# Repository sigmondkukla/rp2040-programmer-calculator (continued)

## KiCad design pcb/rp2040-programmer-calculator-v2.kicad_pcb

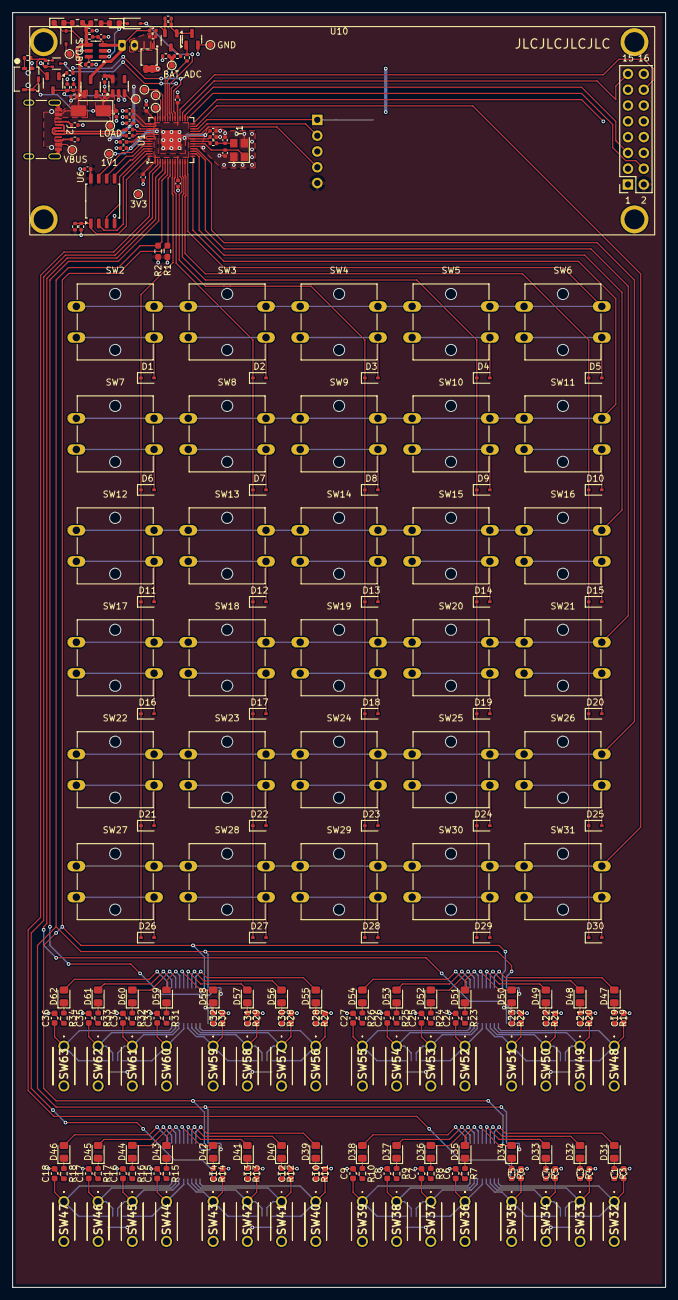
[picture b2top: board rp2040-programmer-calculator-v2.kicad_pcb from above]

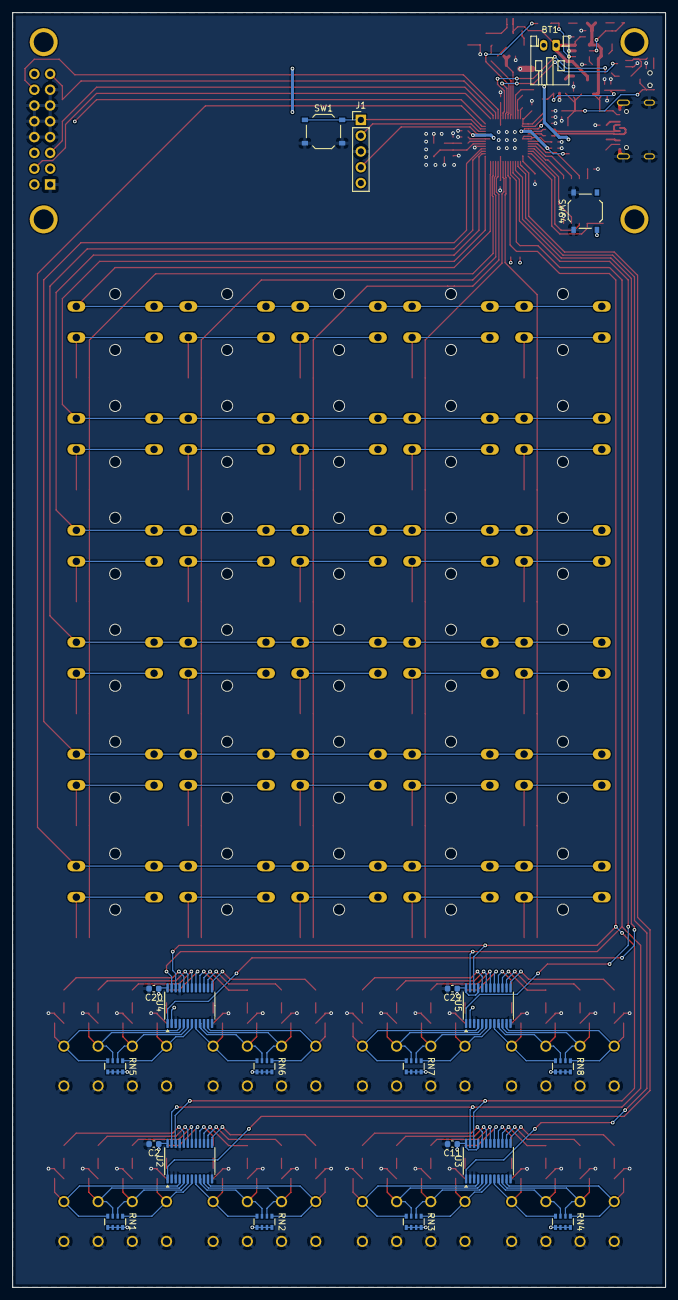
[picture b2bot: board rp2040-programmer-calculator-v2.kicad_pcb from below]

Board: 2 copper layers, 105.0 x 205.0 mm, 283 parts (20 on the bottom side), 196 nets.

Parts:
BT1: 3.7V; JST_PH_S2B-PH-K_1x02_P2.00mm_Horizontal_Reverse_Polarity
C1, C2, C3, C4, C5, C6, C7, C8, C9, C10, C11, C12, C13, C14, C15, C16, C17, C18, C19, C20, C21, C22, C23, C24, C25, C26, C27, C28, C29, C30, C31, C32, C33, C34, C35, C36: 100n; C_0603_1608Metric
C37, C47, C48, C49, C50, C51, C52, C56, C57, C58: 100n; C_0402_1005Metric
C38, C39: 15p; C_0402_1005Metric
C40, C43: 10u; C_0402_1005Metric
C41, C42, C44, C54, C55: 1u; C_0402_1005Metric
C45: 100p; C_0402_1005Metric
C46: 0.1u; C_0402_1005Metric
C53: 470n; C_0402_1005Metric
D1, D2, D3, D4, D5, D6, D7, D8, D9, D10, D11, D12, D13, D14, D15, D16, D17, D18, D19, D20, D21, D22, D23, D24, D25, D26, D27, D28, D29, D30, D66: 1N4148WS; D_SOD-323
D31, D32, D33, D34, D35, D36, D37, D38, D39, D40, D41, D42, D43, D44, D45, D46, D47, D48, D49, D50, D51, D52, D53, D54, D55, D56, D57, D58, D59, D60, D61, D62: IN-S85AT5B; LED_0805_2012Metric_Pad1.15x1.40mm_HandSolder
D63: SS14; D_SMA
D64, D65: KT-0603R; LED_0603_1608Metric
D67: DNP; D_SOD-323
D68: BAT54C; SOT-23-3
J1: Pin Header 1x05 P2.54mm; PinHeader_1x05_P2.54mm_Vertical
J2: USB4105-GF-A; USB_C_Receptacle_GCT_USB4105-xx-A_16P_TopMnt_Horizontal
Q1: AO3401A; SOT-23-3
Q2: BSS84; SOT-23-3
Q3: MMBT3904; SOT-23
Q4: DMG1012T; SOT-523
R1, R2: 4.7k; R_0603_1608Metric_Pad0.98x0.95mm_HandSolder
R3, R4, R5, R6, R7, R8, R9, R10, R11, R12, R13, R14, R15, R16, R17, R18, R19, R20, R21, R22, R23, R24, R25, R26, R27, R28, R29, R30, R31, R32, R33, R34: 270; R_0603_1608Metric
R35, R47, R50, R51: 10k; R_0402_1005Metric
R36, R41, R48, R52, R54: 1k; R_0402_1005Metric
R37, R38: 5.1k; R_0402_1005Metric
R39, R40: 27; R_0402_1005Metric
R42, R43, R53, R55: 100k; R_0402_1005Metric
R44: 2k; R_0402_1005Metric
R45, R46: 2k; R_0603_1608Metric
R49: 330k; R_0402_1005Metric
RN1, RN2, RN3, RN4, RN5, RN6, RN7, RN8: DNP; R_Array_Convex_4x0603
SW1, SW64: PTS526SM20SMTR21 LFS; SW_Push_1P1T_XKB_TS-1187A
SW2, SW3, SW4, SW5, SW6, SW7, SW8, SW9, SW10, SW11, SW12, SW13, SW14, SW15, SW16, SW17, SW18, SW19, SW20, SW21, SW22, SW23, SW24, SW25, SW26, SW27, SW28, SW29, SW30, SW31: B3F; SW_SPST_Omron_B3F-40xx
SW32, SW33, SW34, SW35, SW36, SW37, SW38, SW39, SW40, SW41, SW42, SW43, SW44, SW45, SW46, SW47, SW48, SW49, SW50, SW51, SW52, SW53, SW54, SW55, SW56, SW57, SW58, SW59, SW60, SW61, SW62, SW63: PTS636SL50 LFS; PTS636SL50LFS
SW65: R-667799; R-667799_MIT
TP1: TEST_GPIO27_ADC1; TestPoint_Pad_D1.0mm
TP2: TEST_GPIO28_ADC2; TestPoint_Pad_D1.0mm
TP3: TEST_GPIO29_ADC3; TestPoint_Pad_D1.0mm
TP4: TEST_3V3; TestPoint_Pad_D1.0mm
TP5: TEST_1V1; TestPoint_Pad_D1.0mm
TP6: TEST_VBUS; TestPoint_Pad_D1.0mm
TP7: TEST_BAT_ADC; TestPoint_Pad_D1.0mm
TP8: TEST_GND; TestPoint_Pad_D1.0mm
TP9: TEST_LDO_EN; TestPoint_Pad_D1.0mm
TP10: TEST_LOAD; TestPoint_Pad_D1.0mm
TP11: TEST_STDBY; TestPoint_Pad_D1.0mm
U1: RP2040; QFN-56-1EP_7x7mm_P0.4mm_EP3.2x3.2mm
U2, U3, U4, U5: TCA9555PWR; TSSOP-24_4.4x7.8mm_P0.65mm
U6: W25Q32JVSS; SOIC-8_5.23x5.23mm_P1.27mm
U7: TLV75533PDBV; SOT-23-5
U8: TP4057; TSOT-23-6
U9: XB7608AJ
U10: 3.12" SSD1322 OLED; SSD1322_OLED
Y1: ABM8-272-T3; Crystal_SMD_Abracon_ABM8G-4Pin_3.2x2.5mm

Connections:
+1V1: C47.1, C48.1, C54.1, TP5.1, U1.23 (DVDD), U1.45 (VREG_VOUT), U1.50 (DVDD)
+3V3: C2.1, C11.1, C20.1, C29.1, C37.1, C41.1, C49.1, C50.1, C51.1, C52.1, C55.1, C56.1, C57.1, C58.1, J1.5, R1.2, R2.2, R35.1, RN1.5 (R4.2), RN1.6 (R3.2), RN1.7 (R2.2), RN1.8 (R1.2), RN2.5 (R4.2), RN2.6 (R3.2), RN2.7 (R2.2), RN2.8 (R1.2), RN3.5 (R4.2), RN3.6 (R3.2), RN3.7 (R2.2), RN3.8 (R1.2), RN4.5 (R4.2), RN4.6 (R3.2), RN4.7 (R2.2), RN4.8 (R1.2), RN5.5 (R4.2), RN5.6 (R3.2), RN5.7 (R2.2), RN5.8 (R1.2), RN6.5 (R4.2), RN6.6 (R3.2), RN6.7 (R2.2), RN6.8 (R1.2), RN7.5 (R4.2), RN7.6 (R3.2), RN7.7 (R2.2), RN7.8 (R1.2), RN8.5 (R4.2), RN8.6 (R3.2), RN8.7 (R2.2), RN8.8 (R1.2), TP4.1, U1.1 (IOVDD), U1.10 (IOVDD), U1.22 (IOVDD), U1.33 (IOVDD), U1.42 (IOVDD), U1.43 (ADC_AVDD), U1.44 (VREG_IN), U1.48 (USB_VDD), U1.49 (IOVDD), U2.24 (VCC), U3.21 (A0), U3.24 (VCC), U4.2 (A1), U4.24 (VCC), U5.2 (A1), U5.21 (A0), U5.24 (VCC), U6.8 (VCC), U7.5 (OUT), U10.2 (VCC_IN)
/BAT_ADC: R50.2, R51.1, TP7.1, U1.38 (GPIO26_ADC0)
/BAT_ADC_EN: R49.1, U1.37 (GPIO25)
/BTN_0_INT: U1.2 (GPIO0), U2.1 (~INT)
/BTN_1_INT: U1.3 (GPIO1), U3.1 (~INT)
/BTN_2_INT: U1.4 (GPIO2), U4.1 (~INT)
/BTN_3_INT: U1.5 (GPIO3), U5.1 (~INT)
/Buttons0/BTN_0: C1.1, RN1.4 (R4.1), SW32.1, U2.4 (P00)
/Buttons0/BTN_1: C3.1, RN1.3 (R3.1), SW33.1, U2.5 (P01)
/Buttons0/BTN_2: C4.1, RN1.2 (R2.1), SW34.1, U2.6 (P02)
/Buttons0/BTN_3: C5.1, RN1.1 (R1.1), SW35.1, U2.7 (P03)
/Buttons0/BTN_4: C6.1, RN2.4 (R4.1), SW36.1, U2.8 (P04)
/Buttons0/BTN_5: C7.1, RN2.3 (R3.1), SW37.1, U2.9 (P05)
/Buttons0/BTN_6: C8.1, RN2.2 (R2.1), SW38.1, U2.10 (P06)
/Buttons0/BTN_7: C9.1, RN2.1 (R1.1), SW39.1, U2.11 (P07)
/Buttons0/LED_0: D31.2 (A), U2.20 (P17)
/Buttons0/LED_1: D32.2 (A), U2.19 (P16)
/Buttons0/LED_2: D33.2 (A), U2.18 (P15)
/Buttons0/LED_3: D34.2 (A), U2.17 (P14)
/Buttons0/LED_4: D35.2 (A), U2.16 (P13)
/Buttons0/LED_5: D36.2 (A), U2.15 (P12)
/Buttons0/LED_6: D37.2 (A), U2.14 (P11)
/Buttons0/LED_7: D38.2 (A), U2.13 (P10)
/Buttons1/BTN_0: C10.1, RN3.4 (R4.1), SW40.1, U3.4 (P00)
/Buttons1/BTN_1: C12.1, RN3.3 (R3.1), SW41.1, U3.5 (P01)
/Buttons1/BTN_2: C13.1, RN3.2 (R2.1), SW42.1, U3.6 (P02)
/Buttons1/BTN_3: C14.1, RN3.1 (R1.1), SW43.1, U3.7 (P03)
/Buttons1/BTN_4: C15.1, RN4.4 (R4.1), SW44.1, U3.8 (P04)
/Buttons1/BTN_5: C16.1, RN4.3 (R3.1), SW45.1, U3.9 (P05)
/Buttons1/BTN_6: C17.1, RN4.2 (R2.1), SW46.1, U3.10 (P06)
/Buttons1/BTN_7: C18.1, RN4.1 (R1.1), SW47.1, U3.11 (P07)
/Buttons1/LED_0: D39.2 (A), U3.20 (P17)
/Buttons1/LED_1: D40.2 (A), U3.19 (P16)
/Buttons1/LED_2: D41.2 (A), U3.18 (P15)
/Buttons1/LED_3: D42.2 (A), U3.17 (P14)
/Buttons1/LED_4: D43.2 (A), U3.16 (P13)
/Buttons1/LED_5: D44.2 (A), U3.15 (P12)
/Buttons1/LED_6: D45.2 (A), U3.14 (P11)
/Buttons1/LED_7: D46.2 (A), U3.13 (P10)
/Buttons2/BTN_0: C19.1, RN5.4 (R4.1), SW48.1, U4.4 (P00)
/Buttons2/BTN_1: C21.1, RN5.3 (R3.1), SW49.1, U4.5 (P01)
/Buttons2/BTN_2: C22.1, RN5.2 (R2.1), SW50.1, U4.6 (P02)
/Buttons2/BTN_3: C23.1, RN5.1 (R1.1), SW51.1, U4.7 (P03)
/Buttons2/BTN_4: C24.1, RN6.4 (R4.1), SW52.1, U4.8 (P04)
/Buttons2/BTN_5: C25.1, RN6.3 (R3.1), SW53.1, U4.9 (P05)
/Buttons2/BTN_6: C26.1, RN6.2 (R2.1), SW54.1, U4.10 (P06)
/Buttons2/BTN_7: C27.1, RN6.1 (R1.1), SW55.1, U4.11 (P07)
/Buttons2/LED_0: D47.2 (A), U4.20 (P17)
/Buttons2/LED_1: D48.2 (A), U4.19 (P16)
/Buttons2/LED_2: D49.2 (A), U4.18 (P15)
/Buttons2/LED_3: D50.2 (A), U4.17 (P14)
/Buttons2/LED_4: D51.2 (A), U4.16 (P13)
/Buttons2/LED_5: D52.2 (A), U4.15 (P12)
/Buttons2/LED_6: D53.2 (A), U4.14 (P11)
/Buttons2/LED_7: D54.2 (A), U4.13 (P10)
/Buttons3/BTN_0: C28.1, RN7.4 (R4.1), SW56.1, U5.4 (P00)
/Buttons3/BTN_1: C30.1, RN7.3 (R3.1), SW57.1, U5.5 (P01)
/Buttons3/BTN_2: C31.1, RN7.2 (R2.1), SW58.1, U5.6 (P02)
/Buttons3/BTN_3: C32.1, RN7.1 (R1.1), SW59.1, U5.7 (P03)
/Buttons3/BTN_4: C33.1, RN8.4 (R4.1), SW60.1, U5.8 (P04)
/Buttons3/BTN_5: C34.1, RN8.3 (R3.1), SW61.1, U5.9 (P05)
/Buttons3/BTN_6: C35.1, RN8.2 (R2.1), SW62.1, U5.10 (P06)
/Buttons3/BTN_7: C36.1, RN8.1 (R1.1), SW63.1, U5.11 (P07)
/Buttons3/LED_0: D55.2 (A), U5.20 (P17)
/Buttons3/LED_1: D56.2 (A), U5.19 (P16)
/Buttons3/LED_2: D57.2 (A), U5.18 (P15)
/Buttons3/LED_3: D58.2 (A), U5.17 (P14)
/Buttons3/LED_4: D59.2 (A), U5.16 (P13)
/Buttons3/LED_5: D60.2 (A), U5.15 (P12)
/Buttons3/LED_6: D61.2 (A), U5.14 (P11)
/Buttons3/LED_7: D62.2 (A), U5.13 (P10)
/CHRG: D66.2 (A), U1.36 (GPIO24)
/Crystal/XIN: C38.2, U1.20 (XIN), Y1.1
/Crystal/XOUT: R41.2, U1.21 (XOUT)
/Flash/QSPI_SCLK: U1.52 (QSPI_SCLK), U6.6 (CLK)
/Flash/QSPI_SD0: U1.53 (QSPI_SD0), U6.5 (DI(IO0))
/Flash/QSPI_SD1: U1.55 (QSPI_SD1), U6.2 (DO(IO1))
/Flash/QSPI_SD2: U1.54 (QSPI_SD2), U6.3 (IO2)
/Flash/QSPI_SD3: U1.51 (QSPI_SD3), U6.7 (IO3)
/Flash/QSPI_SS: R35.2, R36.2, U1.56 (QSPI_SS), U6.1 (~CS)
/I2C_SCL: R1.1, U1.7 (GPIO5), U2.22 (SCL), U3.22 (SCL), U4.22 (SCL), U5.22 (SCL)
/I2C_SDA: R2.1, U1.6 (GPIO4), U2.23 (SDA), U3.23 (SDA), U4.23 (SDA), U5.23 (SDA)
/KEYS_COL_1: D1.1 (K), D6.1 (K), D11.1 (K), D16.1 (K), D21.1 (K), D26.1 (K), U1.8 (GPIO6)
/KEYS_COL_2: D2.1 (K), D7.1 (K), D12.1 (K), D17.1 (K), D22.1 (K), D27.1 (K), U1.9 (GPIO7)
/KEYS_COL_3: D3.1 (K), D8.1 (K), D13.1 (K), D18.1 (K), D23.1 (K), D28.1 (K), U1.11 (GPIO8)
/KEYS_COL_4: D4.1 (K), D9.1 (K), D14.1 (K), D19.1 (K), D24.1 (K), D29.1 (K), U1.12 (GPIO9)
/KEYS_COL_5: D5.1 (K), D10.1 (K), D15.1 (K), D20.1 (K), D25.1 (K), D30.1 (K), U1.13 (GPIO10)
/KEYS_ROW_1: SW2.1, SW3.1, SW4.1, SW5.1, SW6.1, U1.14 (GPIO11)
/KEYS_ROW_2: SW7.1, SW8.1, SW9.1, SW10.1, SW11.1, U1.15 (GPIO12)
/KEYS_ROW_3: SW12.1, SW13.1, SW14.1, SW15.1, SW16.1, U1.16 (GPIO13)
/KEYS_ROW_4: SW17.1, SW18.1, SW19.1, SW20.1, SW21.1, U1.17 (GPIO14)
/KEYS_ROW_5: SW22.1, SW23.1, SW24.1, SW25.1, SW26.1, U1.18 (GPIO15)
/KEYS_ROW_6: SW27.1, SW28.1, SW29.1, SW30.1, SW31.1, U1.27 (GPIO16)
/LCD_DC: U1.32 (GPIO21), U10.14 (D/C#)
/LCD_RESET: U1.31 (GPIO20), U10.15 (RES#)
/LCD_SPI_CLK: U1.29 (GPIO18), U10.4 (D0/CLK)
/LCD_SPI_CS: U1.28 (GPIO17), U10.16 (CS#)
/LCD_SPI_DIN: U1.30 (GPIO19), U10.5 (D1/DIN)
/PWR_BTN: Q4.3 (D), U1.35 (GPIO23)
/PWR_EN: R54.1, U1.34 (GPIO22)
/Power/BAT+: BT1.1 (+), C43.1, C45.1, Q1.3 (D), Q2.2 (S), R43.2, R47.1, R48.2, U8.3 (BAT)
/Power/BAT-: BT1.2 (-), C46.2, U9.2 (GND), U9.3 (GND)
/Power/LDO_EN: C53.1, D68.3, R53.1, TP9.1, U7.3 (EN)
/Power/LOAD: C42.1, C44.1, D63.1 (K), Q1.2 (S), SW65.B1, SW65.B2, SW65.B3, TP10.1, U7.1 (IN)
/Power/TP4057_~CHRG: D65.1 (K), D66.1 (K), U8.1 (~CHRG)
/Power/TP4057_~STDBY: D64.1 (K), D67.1 (K), U8.5 (STDBY)
/Power/~STDBY: D67.2 (A), TP11.1
/RUN: J1.1, SW1.1, U1.26 (RUN)
/SWCLK: J1.4, U1.24 (SWCLK)
/SWD: J1.2, U1.25 (SWD)
/USB/USB_D+: J2.A6 (D+), J2.B6 (D+), R40.1
/USB/USB_D-: J2.A7 (D-), J2.B7 (D-), R39.1
/USB/USB_DM: R39.2, U1.46 (USB_DM)
/USB/USB_DP: R40.2, U1.47 (USB_DP)
GND: C1.2, C2.2, C3.2, C4.2, C5.2, C6.2, C7.2, C8.2, C9.2, C10.2, C11.2, C12.2, C13.2, C14.2, C15.2, C16.2, C17.2, C18.2, C19.2, C20.2, C21.2, C22.2, C23.2, C24.2, C25.2, C26.2, C27.2, C28.2, C29.2, C30.2, C31.2, C32.2, C33.2, C34.2, C35.2, C36.2, C37.2, C38.1, C39.1, C40.2, C41.2, C42.2, C43.2, C44.2, C47.2, C48.2, C49.2, C50.2, C51.2, C52.2, C53.2, C54.2, C55.2, C56.2, C57.2, C58.2, J1.3, J2.A1 (GND), J2.A12 (GND), J2.B1 (GND), J2.B12 (GND), J2.S1 (SHIELD), Q3.2 (E), Q4.2 (S), R3.2, R4.2, R5.2, R6.2, R7.2, R8.2, R9.2, R10.2, R11.2, R12.2, R13.2, R14.2, R15.2, R16.2, R17.2, R18.2, R19.2, R20.2, R21.2, R22.2, R23.2, R24.2, R25.2, R26.2, R27.2, R28.2, R29.2, R30.2, R31.2, R32.2, R33.2, R34.2, R37.2, R38.2, R42.2, R44.2, R51.2, R53.2, R55.2, SW1.2, SW32.2, SW33.2, SW34.2, SW35.2, SW36.2, SW37.2, SW38.2, SW39.2, SW40.2, SW41.2, SW42.2, SW43.2, SW44.2, SW45.2, SW46.2, SW47.2, SW48.2, SW49.2, SW50.2, SW51.2, SW52.2, SW53.2, SW54.2, SW55.2, SW56.2, SW57.2, SW58.2, SW59.2, SW60.2, SW61.2, SW62.2, SW63.2, SW64.1, SW65.G, TP8.1, U1.19 (TESTEN), U1.57 (GND), U2.2 (A1), U2.3 (A2), U2.12 (GND), U2.21 (A0), U3.2 (A1), U3.3 (A2), U3.12 (GND), U4.3 (A2), U4.12 (GND), U4.21 (A0), U5.3 (A2), U5.12 (GND), U6.4 (GND), U7.2 (GND), U8.2 (GND), U9.4 (VM), U9.5 (VM), U10.1 (VSS), U10.7 (D3), U10.8 (D4), U10.9 (D5), U10.10 (D6), U10.11 (D7), U10.12 (E/RD#), U10.13 (R/W#), Y1.2, Y1.4
unnamed: C39.2, R41.1, Y1.3
unnamed: D1.2 (A), SW2.2
unnamed: D2.2 (A), SW3.2
unnamed: D3.2 (A), SW4.2
unnamed: D4.2 (A), SW5.2
unnamed: D5.2 (A), SW6.2
unnamed: D6.2 (A), SW7.2
unnamed: D7.2 (A), SW8.2
unnamed: D8.2 (A), SW9.2
unnamed: D9.2 (A), SW10.2
unnamed: D10.2 (A), SW11.2
unnamed: D11.2 (A), SW12.2
unnamed: D12.2 (A), SW13.2
unnamed: D13.2 (A), SW14.2
unnamed: D14.2 (A), SW15.2
unnamed: D15.2 (A), SW16.2
unnamed: D16.2 (A), SW17.2
unnamed: D17.2 (A), SW18.2
unnamed: D18.2 (A), SW19.2
unnamed: D19.2 (A), SW20.2
unnamed: D20.2 (A), SW21.2
unnamed: D21.2 (A), SW22.2
unnamed: D22.2 (A), SW23.2
unnamed: D23.2 (A), SW24.2
unnamed: D24.2 (A), SW25.2
unnamed: D25.2 (A), SW26.2
unnamed: D26.2 (A), SW27.2
unnamed: D27.2 (A), SW28.2
unnamed: D28.2 (A), SW29.2
unnamed: D29.2 (A), SW30.2
unnamed: D30.2 (A), SW31.2
unnamed: D31.1 (K), R3.1
unnamed: D32.1 (K), R4.1
unnamed: D33.1 (K), R5.1
unnamed: D34.1 (K), R6.1
unnamed: D35.1 (K), R7.1
unnamed: D36.1 (K), R8.1
unnamed: D37.1 (K), R9.1
unnamed: D38.1 (K), R10.1
unnamed: D39.1 (K), R11.1
unnamed: D40.1 (K), R12.1
unnamed: D41.1 (K), R13.1
unnamed: D42.1 (K), R14.1
unnamed: D43.1 (K), R15.1
unnamed: D44.1 (K), R16.1
unnamed: D45.1 (K), R17.1
unnamed: D46.1 (K), R18.1
unnamed: D47.1 (K), R19.1
unnamed: D48.1 (K), R20.1
unnamed: D49.1 (K), R21.1
unnamed: D50.1 (K), R22.1
unnamed: D51.1 (K), R23.1
unnamed: D52.1 (K), R24.1
unnamed: D53.1 (K), R25.1
unnamed: D54.1 (K), R26.1
unnamed: D55.1 (K), R27.1
unnamed: D56.1 (K), R28.1
unnamed: D57.1 (K), R29.1
unnamed: D58.1 (K), R30.1
unnamed: D59.1 (K), R31.1
unnamed: D60.1 (K), R32.1
unnamed: D61.1 (K), R33.1
unnamed: D62.1 (K), R34.1
unnamed: D64.2 (A), R45.2
unnamed: D65.2 (A), R46.2
unnamed: D68.1, R54.2
unnamed: J2.A5 (CC1), R37.1
unnamed: J2.B5 (CC2), R38.1
unnamed: Q2.3 (D), R50.1
unnamed: C45.2, Q2.1 (G), Q3.3 (C), R47.2
unnamed: Q3.1 (B), R49.2
unnamed: D68.2, Q4.1 (G), R52.2, R55.1
unnamed: R36.1, SW64.2
unnamed: R52.1, SW65.A
unnamed: TP1.1, U1.39 (GPIO27_ADC1)
unnamed: TP2.1, U1.40 (GPIO28_ADC2)
unnamed: TP3.1, U1.41 (GPIO29_ADC3)
unnamed: R44.1, U8.6 (PROG)
unnamed: C46.1, R48.1, U9.1 (VDD)
VBUS: C40.1, D63.2 (A), J2.A4 (VBUS), J2.A9 (VBUS), J2.B4 (VBUS), J2.B9 (VBUS), Q1.1 (G), R42.1, R43.1, R45.1, R46.1, TP6.1, U8.4 (V_{CC})

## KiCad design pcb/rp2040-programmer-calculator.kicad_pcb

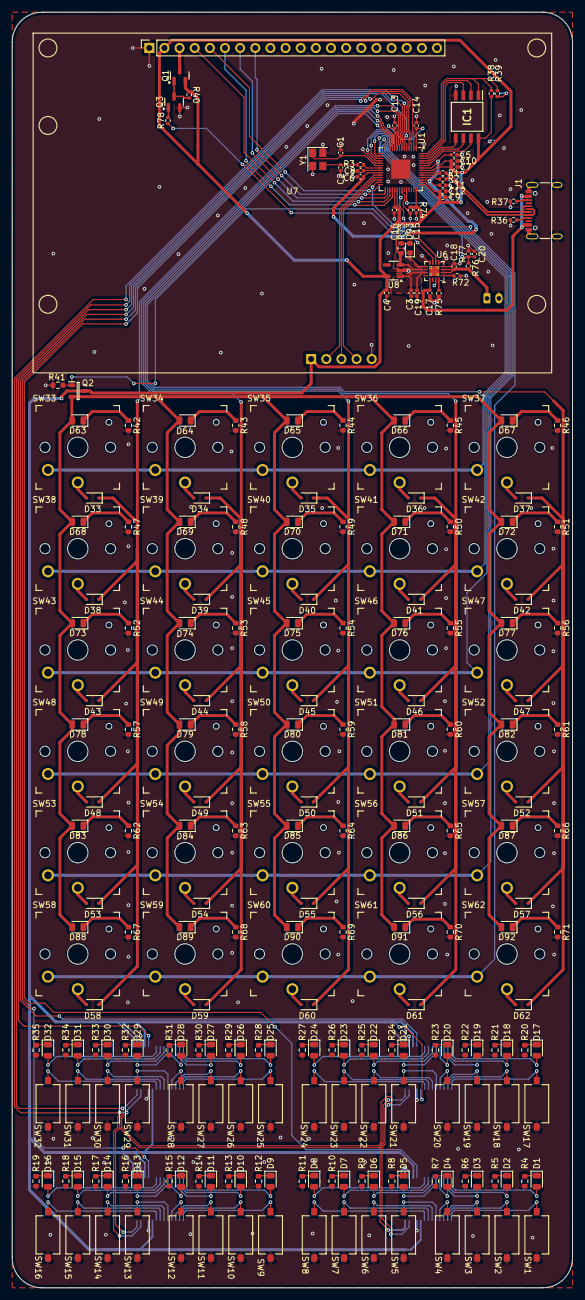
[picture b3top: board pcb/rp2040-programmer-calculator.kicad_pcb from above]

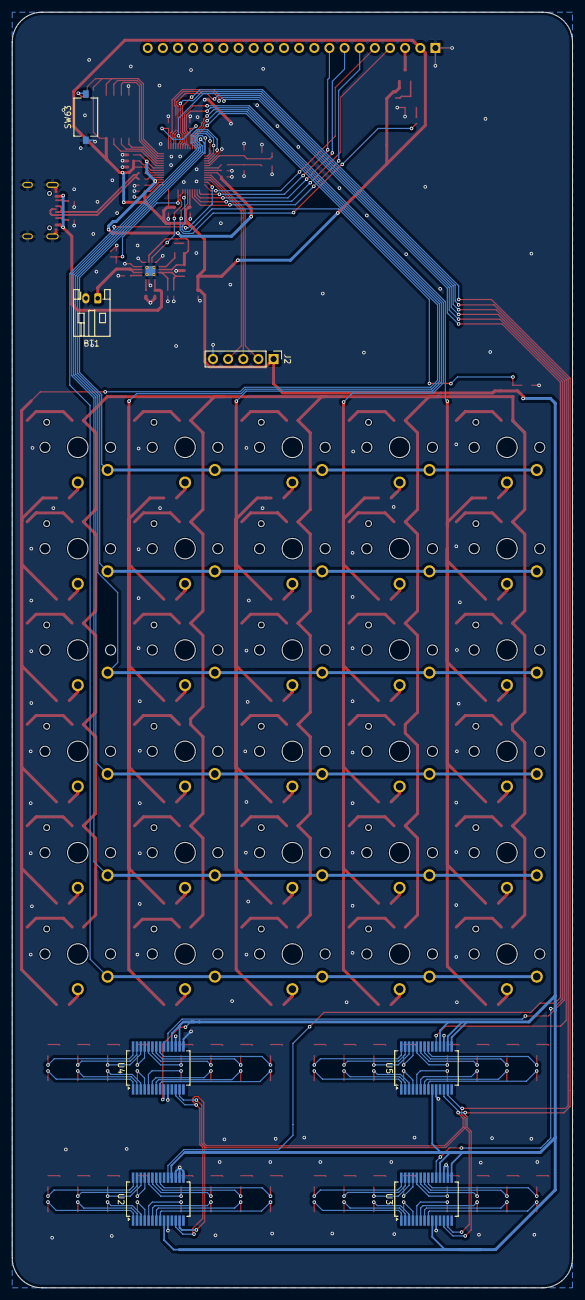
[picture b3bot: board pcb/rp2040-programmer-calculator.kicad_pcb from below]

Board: 2 copper layers, 94.0 x 214.0 mm, 270 parts (7 on the bottom side), 215 nets.

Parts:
BT1: 3.7V; JST_PH_S2B-PH-K_1x02_P2.00mm_Horizontal_Reverse_Polarity
C1, C2: 15p; C_0402_1005Metric
C3, C4, C11, C12, C17: 1u; C_0402_1005Metric
C5, C6, C7, C8, C9, C10, C13, C14, C15, C16, C20: 100n; C_0402_1005Metric
C18, C19: 4.7u; C_0402_1005Metric
D1, D2, D3, D4, D5, D6, D7, D8, D9, D10, D11, D12, D13, D14, D15, D16, D17, D18, D19, D20, D21, D22, D23, D24, D25, D26, D27, D28, D29, D30, D31, D32, D63, D64, D65, D66, D67, D68, D69, D70, D71, D72, D73, D74, D75, D76, D77, D78, D79, D80, D81, D82, D83, D84, D85, D86, D87, D88, D89, D90, D91, D92: KT-0805B; D_0805_2012Metric
D33, D34, D35, D36, D37, D38, D39, D40, D41, D42, D43, D44, D45, D46, D47, D48, D49, D50, D51, D52, D53, D54, D55, D56, D57, D58, D59, D60, D61, D62: 1N4148; D_SOD-323
D93: KT-0603R; LED_0603_1608Metric
IC1: W25Q16JVSSIQ; SOIC127P790X216-8N
J1: USB_C_Receptacle_USB2.0_16P; USB_C_Receptacle_GCT_USB4105-xx-A_16P_TopMnt_Horizontal
J2: Conn_01x05_Pin; PinHeader_1x05_P2.54mm_Vertical
Q1: SI2301CDS-T1-GE3; SOT-23
Q2: DMN3731U-7; SOT96P240X110-3N
Q3: MMBT3904; SOT-23
R1, R2: 27.4; R_0402_1005Metric
R3, R39: 1k; R_0402_1005Metric
R4, R5, R6, R7, R8, R9, R10, R11, R12, R13, R14, R15, R16, R17, R18, R19, R20, R21, R22, R23, R24, R25, R26, R27, R28, R29, R30, R31, R32, R33, R34, R35: 400; R_0603_1608Metric
R36, R37: 5.1k; R_0402_1005Metric
R38, R40, R72, R74, R78: 10k; R_0402_1005Metric
R41: 10k; R_0603_1608Metric
R42, R43, R44, R45, R46, R47, R48, R49, R50, R51, R52, R53, R54, R55, R56, R57, R58, R59, R60, R61, R62, R63, R64, R65, R66, R67, R68, R69, R70, R71: 80; R_0603_1608Metric
R73: 2k; R_0603_1608Metric
R75: 2.2k; R_0402_1005Metric
R76, R77: 100k; R_0402_1005Metric
SW1, SW2, SW3, SW4, SW5, SW6, SW7, SW8, SW9, SW10, SW11, SW12, SW13, SW14, SW15, SW16, SW17, SW18, SW19, SW20, SW21, SW22, SW23, SW24, SW25, SW26, SW27, SW28, SW29, SW30, SW31, SW32, SW63: SW_Push; SW_Tactile_SPST_NO_Straight_CK_PTS636Sx25SMTRLFS
SW33, SW34, SW35, SW36, SW37, SW38, SW39, SW40, SW41, SW42, SW43, SW44, SW45, SW46, SW47, SW48, SW49, SW50, SW51, SW52, SW53, SW54, SW55, SW56, SW57, SW58, SW59, SW60, SW61, SW62: SW_Push; SW_PG1350
U1: RP2040; QFN-56-1EP_7x7mm_P0.4mm_EP3.2x3.2mm
U2, U3, U4, U5: MCP23017_SS; SSOP-28_5.3x10.2mm_P0.65mm
U6: BQ24230RGT; VQFN-16-1EP_3x3mm_P0.5mm_EP1.68x1.68mm_ThermalVias
U7: LG12864U
U8: TLV75533PDBV; SOT-23-5
Y1: ABM8-272-T3; Crystal_SMD_Abracon_ABM8G-4Pin_3.2x2.5mm

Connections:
+1V1: C5.1, C6.1, C11.1, U1.23 (DVDD), U1.45 (VREG_VOUT), U1.50 (DVDD)
+3V3: C4.1, C7.1, C8.1, C9.1, C10.1, C12.1, C13.1, C14.1, C15.1, C16.1, IC1.8 (VCC), J2.1, Q1.2 (S), Q2.3 (D), R38.1, R40.1, R74.1, U1.1 (IOVDD), U1.10 (IOVDD), U1.22 (IOVDD), U1.33 (IOVDD), U1.42 (IOVDD), U1.43 (ADC_AVDD), U1.44 (VREG_IN), U1.48 (USB_VDD), U1.49 (IOVDD), U2.9 (VDD), U2.18 (~RESET), U3.9 (VDD), U3.15 (A0), U3.18 (~RESET), U4.9 (VDD), U4.16 (A1), U4.18 (~RESET), U5.9 (VDD), U5.15 (A0), U5.16 (A1), U5.18 (~RESET), U7.2 (VDD), U8.5 (OUT)
/BTN0_INT: U1.2 (GPIO0), U2.19 (INTB)
/BTN1_INT: U1.3 (GPIO1), U3.19 (INTB)
/BTN2_INT: U1.4 (GPIO2), U4.19 (INTB)
/BTN3_INT: U1.5 (GPIO3), U5.19 (INTB)
/Backlight/LEDA: D63.2 (A), D64.2 (A), D65.2 (A), D66.2 (A), D67.2 (A), D68.2 (A), D69.2 (A), D70.2 (A), D71.2 (A), D72.2 (A), D73.2 (A), D74.2 (A), D75.2 (A), D76.2 (A), D77.2 (A), D78.2 (A), D79.2 (A), D80.2 (A), D81.2 (A), D82.2 (A), D83.2 (A), D84.2 (A), D85.2 (A), D86.2 (A), D87.2 (A), D88.2 (A), D89.2 (A), D90.2 (A), D91.2 (A), D92.2 (A), Q2.2 (S)
/Buttons0/BTN0: SW1.1, U2.1 (GPB0)
/Buttons0/BTN1: SW2.1, U2.2 (GPB1)
/Buttons0/BTN2: SW3.1, U2.3 (GPB2)
/Buttons0/BTN3: SW4.1, U2.4 (GPB3)
/Buttons0/BTN4: SW5.1, U2.5 (GPB4)
/Buttons0/BTN5: SW6.1, U2.6 (GPB5)
/Buttons0/BTN6: SW7.1, U2.7 (GPB6)
/Buttons0/BTN7: SW8.1, U2.8 (GPB7)
/Buttons0/LED0: D1.2 (A), U2.28 (GPA7)
/Buttons0/LED1: D2.2 (A), U2.27 (GPA6)
/Buttons0/LED2: D3.2 (A), U2.26 (GPA5)
/Buttons0/LED3: D4.2 (A), U2.25 (GPA4)
/Buttons0/LED4: D5.2 (A), U2.24 (GPA3)
/Buttons0/LED5: D6.2 (A), U2.23 (GPA2)
/Buttons0/LED6: D7.2 (A), U2.22 (GPA1)
/Buttons0/LED7: D8.2 (A), U2.21 (GPA0)
/Buttons1/BTN0: SW9.1, U3.1 (GPB0)
/Buttons1/BTN1: SW10.1, U3.2 (GPB1)
/Buttons1/BTN2: SW11.1, U3.3 (GPB2)
/Buttons1/BTN3: SW12.1, U3.4 (GPB3)
/Buttons1/BTN4: SW13.1, U3.5 (GPB4)
/Buttons1/BTN5: SW14.1, U3.6 (GPB5)
/Buttons1/BTN6: SW15.1, U3.7 (GPB6)
/Buttons1/BTN7: SW16.1, U3.8 (GPB7)
/Buttons1/LED0: D9.2 (A), U3.28 (GPA7)
/Buttons1/LED1: D10.2 (A), U3.27 (GPA6)
/Buttons1/LED2: D11.2 (A), U3.26 (GPA5)
/Buttons1/LED3: D12.2 (A), U3.25 (GPA4)
/Buttons1/LED4: D13.2 (A), U3.24 (GPA3)
/Buttons1/LED5: D14.2 (A), U3.23 (GPA2)
/Buttons1/LED6: D15.2 (A), U3.22 (GPA1)
/Buttons1/LED7: D16.2 (A), U3.21 (GPA0)
/Buttons2/BTN0: SW17.1, U4.1 (GPB0)
/Buttons2/BTN1: SW18.1, U4.2 (GPB1)
/Buttons2/BTN2: SW19.1, U4.3 (GPB2)
/Buttons2/BTN3: SW20.1, U4.4 (GPB3)
/Buttons2/BTN4: SW21.1, U4.5 (GPB4)
/Buttons2/BTN5: SW22.1, U4.6 (GPB5)
/Buttons2/BTN6: SW23.1, U4.7 (GPB6)
/Buttons2/BTN7: SW24.1, U4.8 (GPB7)
/Buttons2/LED0: D17.2 (A), U4.28 (GPA7)
/Buttons2/LED1: D18.2 (A), U4.27 (GPA6)
/Buttons2/LED2: D19.2 (A), U4.26 (GPA5)
/Buttons2/LED3: D20.2 (A), U4.25 (GPA4)
/Buttons2/LED4: D21.2 (A), U4.24 (GPA3)
/Buttons2/LED5: D22.2 (A), U4.23 (GPA2)
/Buttons2/LED6: D23.2 (A), U4.22 (GPA1)
/Buttons2/LED7: D24.2 (A), U4.21 (GPA0)
/Buttons3/BTN0: SW25.1, U5.1 (GPB0)
/Buttons3/BTN1: SW26.1, U5.2 (GPB1)
/Buttons3/BTN2: SW27.1, U5.3 (GPB2)
/Buttons3/BTN3: SW28.1, U5.4 (GPB3)
/Buttons3/BTN4: SW29.1, U5.5 (GPB4)
/Buttons3/BTN5: SW30.1, U5.6 (GPB5)
/Buttons3/BTN6: SW31.1, U5.7 (GPB6)
/Buttons3/BTN7: SW32.1, U5.8 (GPB7)
/Buttons3/LED0: D25.2 (A), U5.28 (GPA7)
/Buttons3/LED1: D26.2 (A), U5.27 (GPA6)
/Buttons3/LED2: D27.2 (A), U5.26 (GPA5)
/Buttons3/LED3: D28.2 (A), U5.25 (GPA4)
/Buttons3/LED4: D29.2 (A), U5.24 (GPA3)
/Buttons3/LED5: D30.2 (A), U5.23 (GPA2)
/Buttons3/LED6: D31.2 (A), U5.22 (GPA1)
/Buttons3/LED7: D32.2 (A), U5.21 (GPA0)
/Display/LEDA: Q1.3 (D), U7.3 (LEDA)
/Flash/QSPI_SCLK: IC1.6 (CLK), U1.52 (QSPI_SCLK)
/Flash/QSPI_SD0: IC1.5 (DI_(IO0)), U1.53 (QSPI_SD0)
/Flash/QSPI_SD1: IC1.2 (DO_(IO1)), U1.55 (QSPI_SD1)
/Flash/QSPI_SD2: IC1.3 (~WP_(IO2)), U1.54 (QSPI_SD2)
/Flash/QSPI_SD3: IC1.7 (~HOLD_OR_/RESET_(IO3)), U1.51 (QSPI_SD3)
/Flash/QSPI_SS: IC1.1 (~CS), R38.2, R39.2, U1.56 (QSPI_SS)
/I2C_SCL: U1.7 (GPIO5), U2.12 (SCK), U3.12 (SCK), U4.12 (SCK), U5.12 (SCK)
/I2C_SDA: U1.6 (GPIO4), U2.13 (SDA), U3.13 (SDA), U4.13 (SDA), U5.13 (SDA)
/KEYS_LED_PWM: Q2.1 (G), R41.1, U1.35 (GPIO23)
/KEYS_X0: D33.1 (K), D38.1 (K), D43.1 (K), D48.1 (K), D53.1 (K), D58.1 (K), U1.8 (GPIO6)
/KEYS_X1: D34.1 (K), D39.1 (K), D44.1 (K), D49.1 (K), D54.1 (K), D59.1 (K), U1.9 (GPIO7)
/KEYS_X2: D35.1 (K), D40.1 (K), D45.1 (K), D50.1 (K), D55.1 (K), D60.1 (K), U1.11 (GPIO8)
/KEYS_X3: D36.1 (K), D41.1 (K), D46.1 (K), D51.1 (K), D56.1 (K), D61.1 (K), U1.12 (GPIO9)
/KEYS_X4: D37.1 (K), D42.1 (K), D47.1 (K), D52.1 (K), D57.1 (K), D62.1 (K), U1.13 (GPIO10)
/KEYS_Y0: SW33.2, SW34.2, SW35.2, SW36.2, SW37.2, U1.14 (GPIO11)
/KEYS_Y1: SW38.2, SW39.2, SW40.2, SW41.2, SW42.2, U1.15 (GPIO12)
/KEYS_Y2: SW43.2, SW44.2, SW45.2, SW46.2, SW47.2, U1.16 (GPIO13)
/KEYS_Y3: SW48.2, SW49.2, SW50.2, SW51.2, SW52.2, U1.17 (GPIO14)
/KEYS_Y4: SW53.2, SW54.2, SW55.2, SW56.2, SW57.2, U1.18 (GPIO15)
/KEYS_Y5: SW58.2, SW59.2, SW60.2, SW61.2, SW62.2, U1.27 (GPIO16)
/LCD_A0: U1.31 (GPIO20), U7.4 (A0)
/LCD_CS: U1.28 (GPIO17), U7.5 (/CS1)
/LCD_LED_PWM: R78.1, U1.34 (GPIO22)
/LCD_RESET: U1.32 (GPIO21), U7.6 (/RES)
/LCD_SCL: U1.29 (GPIO18), U7.8 (D6_(SCL))
/LCD_SDI: U1.30 (GPIO19), U7.7 (D7_(SI))
/Power/CHARGER_OUT: C3.1, C19.1, R73.2, U6.6 (EN1), U6.10 (OUT), U6.11 (OUT), U8.1 (IN), U8.3 (EN)
/Power/D+: J1.A6 (D+), J1.B6 (D+), R1.1
/Power/D-: J1.A7 (D-), J1.B7 (D-), R2.1
/RUN: J2.4, U1.26 (RUN)
/SWCLK: J2.2, U1.24 (SWCLK)
/SWD: J2.3, U1.25 (SWD)
/VBAT_MEASURE: C20.1, R76.2, R77.1, U1.38 (GPIO26_ADC0)
/~PGOOD: R74.2, U1.36 (GPIO24), U6.7 (PGOOD)
GND: BT1.2 (-), C1.1, C2.1, C3.2, C4.2, C5.2, C6.2, C7.2, C8.2, C9.2, C10.2, C11.2, C12.2, C13.2, C14.2, C15.2, C16.2, C17.2, C18.2, C19.2, C20.2, IC1.4 (GND), J1.A1 (GND), J1.A12 (GND), J1.B1 (GND), J1.B12 (GND), J1.S1 (SHIELD), J2.5, Q3.2 (E), R4.2, R5.2, R6.2, R7.2, R8.2, R9.2, R10.2, R11.2, R12.2, R13.2, R14.2, R15.2, R16.2, R17.2, R18.2, R19.2, R20.2, R21.2, R22.2, R23.2, R24.2, R25.2, R26.2, R27.2, R28.2, R29.2, R30.2, R31.2, R32.2, R33.2, R34.2, R35.2, R36.2, R37.2, R41.2, R42.2, R43.2, R44.2, R45.2, R46.2, R47.2, R48.2, R49.2, R50.2, R51.2, R52.2, R53.2, R54.2, R55.2, R56.2, R57.2, R58.2, R59.2, R60.2, R61.2, R62.2, R63.2, R64.2, R65.2, R66.2, R67.2, R68.2, R69.2, R70.2, R71.2, R72.1, R75.1, R77.2, SW1.2, SW2.2, SW3.2, SW4.2, SW5.2, SW6.2, SW7.2, SW8.2, SW9.2, SW10.2, SW11.2, SW12.2, SW13.2, SW14.2, SW15.2, SW16.2, SW17.2, SW18.2, SW19.2, SW20.2, SW21.2, SW22.2, SW23.2, SW24.2, SW25.2, SW26.2, SW27.2, SW28.2, SW29.2, SW30.2, SW31.2, SW32.2, SW63.1, U1.19 (TESTEN), U1.57 (GND), U2.10 (VSS), U2.15 (A0), U2.16 (A1), U2.17 (A2), U3.10 (VSS), U3.16 (A1), U3.17 (A2), U4.10 (VSS), U4.15 (A0), U4.17 (A2), U5.10 (VSS), U5.17 (A2), U6.4 (CE), U6.5 (EN2), U6.8 (VSS), U6.15 (TD), U6.17 (VSS), U7.1 (VSS), U8.2 (GND), Y1.2, Y1.4
unnamed: C2.2, R3.1, Y1.3
unnamed: D1.1 (K), R4.1
unnamed: D2.1 (K), R5.1
unnamed: D3.1 (K), R6.1
unnamed: D4.1 (K), R7.1
unnamed: D5.1 (K), R8.1
unnamed: D6.1 (K), R9.1
unnamed: D7.1 (K), R10.1
unnamed: D8.1 (K), R11.1
unnamed: D9.1 (K), R12.1
unnamed: D10.1 (K), R13.1
unnamed: D11.1 (K), R14.1
unnamed: D12.1 (K), R15.1
unnamed: D13.1 (K), R16.1
unnamed: D14.1 (K), R17.1
unnamed: D15.1 (K), R18.1
unnamed: D16.1 (K), R19.1
unnamed: D17.1 (K), R20.1
unnamed: D18.1 (K), R21.1
unnamed: D19.1 (K), R22.1
unnamed: D20.1 (K), R23.1
unnamed: D21.1 (K), R24.1
unnamed: D22.1 (K), R25.1
unnamed: D23.1 (K), R26.1
unnamed: D24.1 (K), R27.1
unnamed: D25.1 (K), R28.1
unnamed: D26.1 (K), R29.1
unnamed: D27.1 (K), R30.1
unnamed: D28.1 (K), R31.1
unnamed: D29.1 (K), R32.1
unnamed: D30.1 (K), R33.1
unnamed: D31.1 (K), R34.1
unnamed: D32.1 (K), R35.1
unnamed: D33.2 (A), SW33.1
unnamed: D34.2 (A), SW34.1
unnamed: D35.2 (A), SW35.1
unnamed: D36.2 (A), SW36.1
unnamed: D37.2 (A), SW37.1
unnamed: D38.2 (A), SW38.1
unnamed: D39.2 (A), SW39.1
unnamed: D40.2 (A), SW40.1
unnamed: D41.2 (A), SW41.1
unnamed: D42.2 (A), SW42.1
unnamed: D43.2 (A), SW43.1
unnamed: D44.2 (A), SW44.1
unnamed: D45.2 (A), SW45.1
unnamed: D46.2 (A), SW46.1
unnamed: D47.2 (A), SW47.1
unnamed: D48.2 (A), SW48.1
unnamed: D49.2 (A), SW49.1
unnamed: D50.2 (A), SW50.1
unnamed: D51.2 (A), SW51.1
unnamed: D52.2 (A), SW52.1
unnamed: D53.2 (A), SW53.1
unnamed: D54.2 (A), SW54.1
unnamed: D55.2 (A), SW55.1
unnamed: D56.2 (A), SW56.1
unnamed: D57.2 (A), SW57.1
unnamed: D58.2 (A), SW58.1
unnamed: D59.2 (A), SW59.1
unnamed: D60.2 (A), SW60.1
unnamed: D61.2 (A), SW61.1
unnamed: D62.2 (A), SW62.1
unnamed: D63.1 (K), R42.1
unnamed: D64.1 (K), R43.1
unnamed: D65.1 (K), R44.1
unnamed: D66.1 (K), R45.1
unnamed: D67.1 (K), R46.1
unnamed: D68.1 (K), R47.1
unnamed: D69.1 (K), R48.1
unnamed: D70.1 (K), R49.1
unnamed: D71.1 (K), R50.1
unnamed: D72.1 (K), R51.1
unnamed: D73.1 (K), R52.1
unnamed: D74.1 (K), R53.1
unnamed: D75.1 (K), R54.1
unnamed: D76.1 (K), R55.1
unnamed: D77.1 (K), R56.1
unnamed: D78.1 (K), R57.1
unnamed: D79.1 (K), R58.1
unnamed: D80.1 (K), R59.1
unnamed: D81.1 (K), R60.1
unnamed: D82.1 (K), R61.1
unnamed: D83.1 (K), R62.1
unnamed: D84.1 (K), R63.1
unnamed: D85.1 (K), R64.1
unnamed: D86.1 (K), R65.1
unnamed: D87.1 (K), R66.1
unnamed: D88.1 (K), R67.1
unnamed: D89.1 (K), R68.1
unnamed: D90.1 (K), R69.1
unnamed: D91.1 (K), R70.1
unnamed: D92.1 (K), R71.1
unnamed: D93.2 (A), R73.1
unnamed: D93.1 (K), U6.9 (CHG)
unnamed: J1.A5 (CC1), R36.1
unnamed: J1.B5 (CC2), R37.1
unnamed: Q1.1 (G), Q3.3 (C), R40.2
unnamed: Q3.1 (B), R78.2
unnamed: R39.1, SW63.2
unnamed: R2.2, U1.46 (USB_DM)
unnamed: R1.2, U1.47 (USB_DP)
unnamed: C1.2, U1.20 (XIN), Y1.1
unnamed: R3.2, U1.21 (XOUT)
unnamed: R75.2, U6.16 (ISET)
unnamed: R72.2, U6.1 (TS)
VBAT: BT1.1 (+), C18.1, R76.1, U6.2 (BAT), U6.3 (BAT)
VBUS: C17.1, J1.A4 (VBUS), J1.A9 (VBUS), J1.B4 (VBUS), J1.B9 (VBUS), U6.13 (IN)

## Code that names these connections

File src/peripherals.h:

#ifndef PERIPHERALS_H
#define PERIPHERALS_H

// TCA8418 TCA8418 scanner
#define TCA8418_I2C_PORT i2c1
#define TCA8418_I2C_SPEED 400 * 1000 // 400 kHz
#define TCA8418_I2C_ADDR 0x34
#define TCA8418_I2C_SDA 0
#define TCA8418_I2C_SCL 1
#define TCA8418_INT 2
#define TCA8418_RESET 3

// 4 reserved

// SSD1322 256x64 OLED display
#define OLED_SPI_PORT spi0
#define OLED_SPI_SPEED 3000 * 1000 // 3 MHz, 3.333 MHz max for SSD1322
#define OLED_CS 5
#define OLED_SPI_CLK 6
#define OLED_SPI_DIN 7
#define OLED_DC 8
#define OLED_RESET 9
// 10-13 reserved
#define LED_SRCLK 14
#define LED_SER 15
#define LED_SRCLR 16
#define LED_RCLK 17
#define LED_OE 18

#define CHARGER_STDBY 19
#define CHARGER_CHRG 20
// 21 reserved
#define POWER_EN 22
#define POWER_BTN 23
// 24 reserved
#define BAT_ADC_EN 25
#define BAT_ADC 26
// 27-29 spare GPIO connected to header

#endif

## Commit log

2025-01-18 Add KiCad gitignore
2025-01-18 Add pcb v1
2025-01-18 Add pcb v2
2025-01-18 Add pcb v3
2025-01-27 Add some symbol libraries
2025-01-27 Add schematics
2025-01-27 Finish schematic
2025-01-30 Finish PCB
2025-03-16 Finished design
2025-03-16 Update submodule
2025-03-18 Add RP2040 project
2025-03-21 Add u8g2 submodule
2025-03-21 Add TCA8418 driver
2025-03-21 Add pin and port defs
2025-03-21 Begin main structure
2025-03-21 Add images for u8g2
2025-03-21 Add u8g2 calculator example code
2025-03-21 Add TCA8418 datasheet
2025-03-21 Add inkscape keycaps design
2025-03-21 Add basic key interpretation
2025-03-21 Add shift register datasheet
2025-03-21 Add bit leds shift register driver
2025-03-21 Add bit leds init
2025-03-21 Add remaining datasheets
2025-03-21 Cleanup Lopaka output
2025-03-21 Format
2025-03-21 Setup soft power init and latching
